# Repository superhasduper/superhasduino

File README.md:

# superhasduino
its a comercial prototiping board
if you want to access the pcb files use kicad

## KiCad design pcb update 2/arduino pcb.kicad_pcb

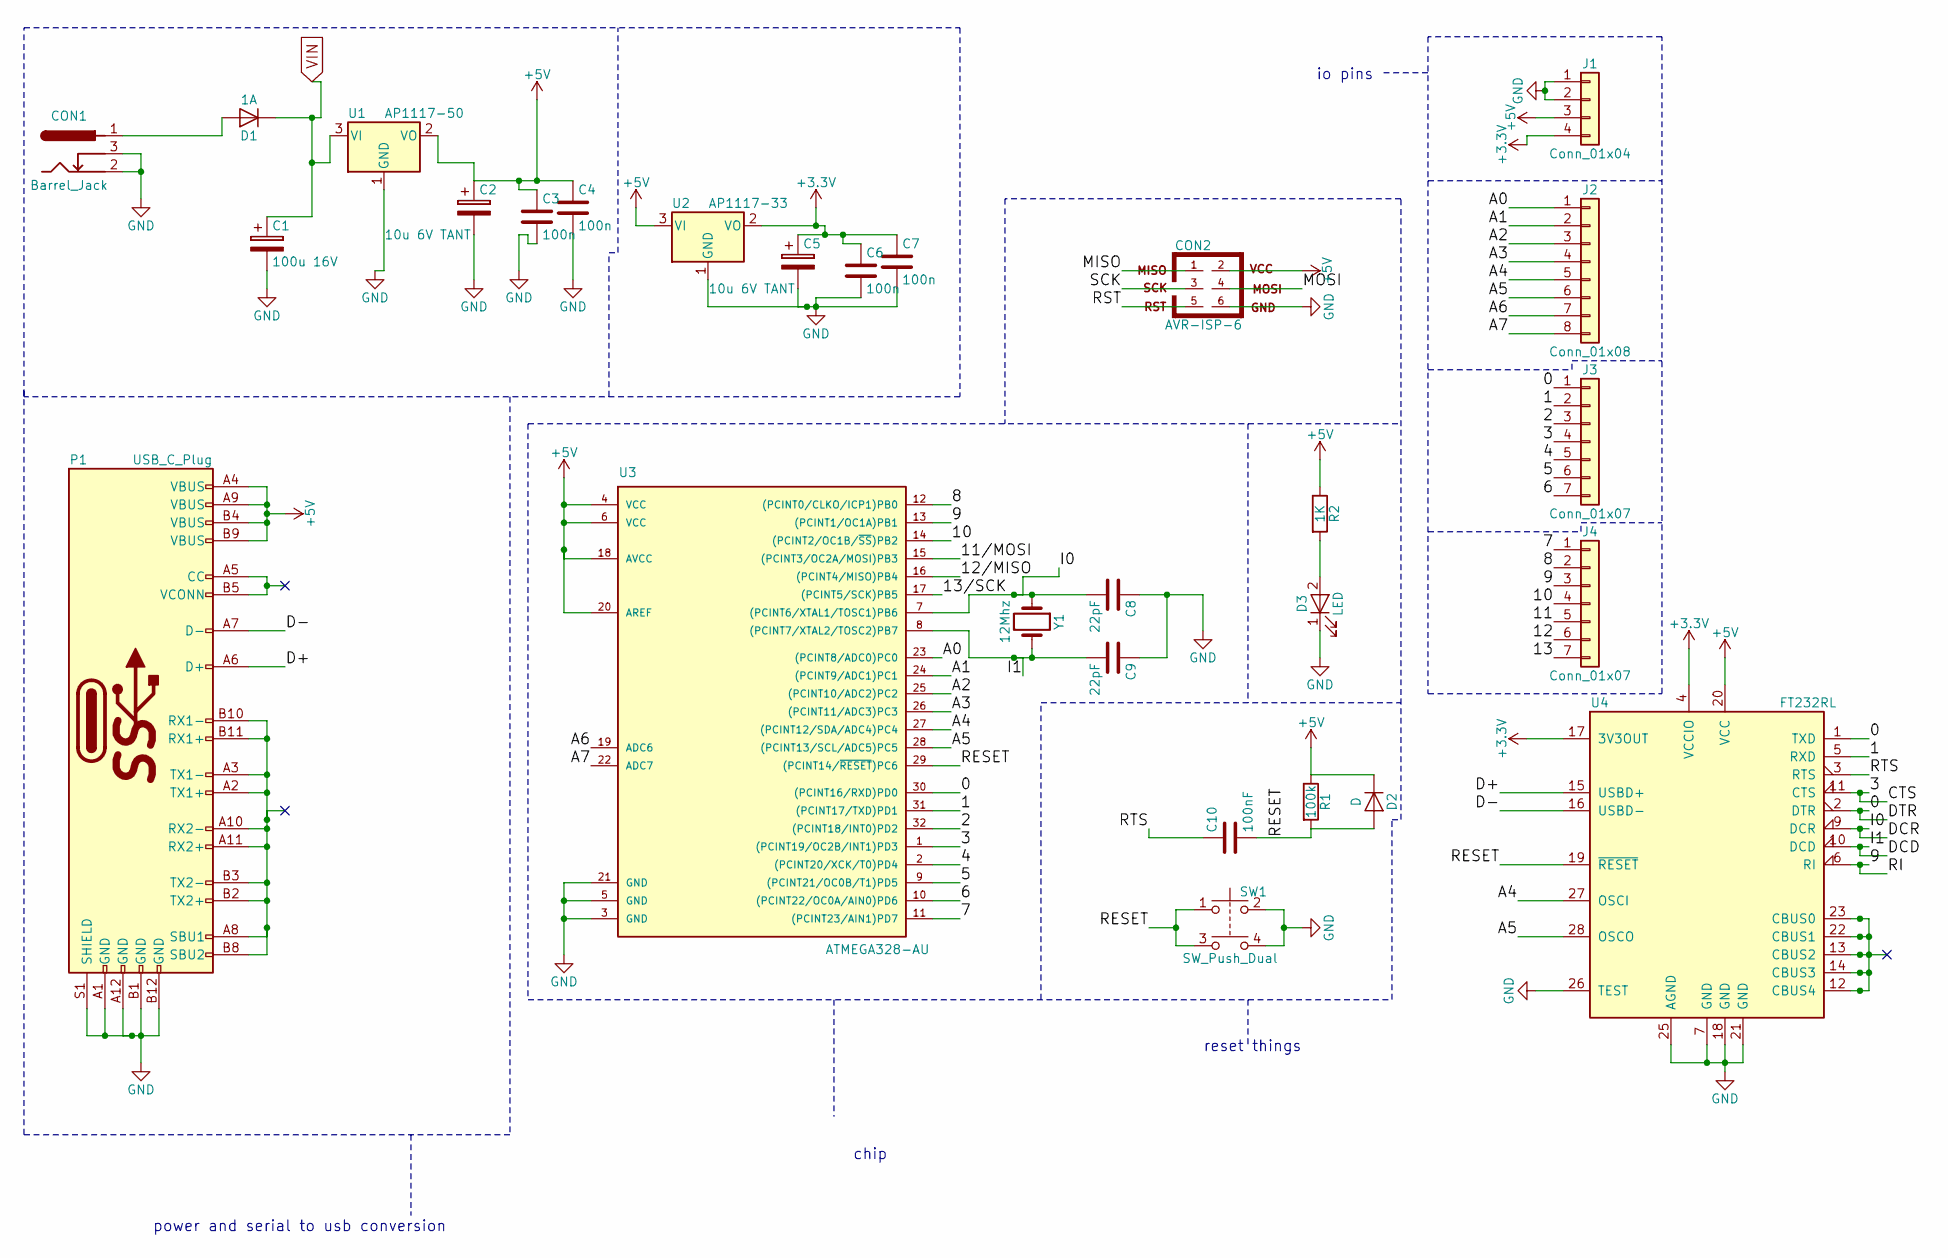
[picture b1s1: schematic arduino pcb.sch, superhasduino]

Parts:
C1: 100u 16V; CP_Radial_D4.0mm_P2.00mm
C2, C5: 10u 6V TANT; CP_Radial_D4.0mm_P2.00mm
C3, C4, C6, C7: 100n; C_1206_HandSoldering
C8, C9: 22pF; C_1206_HandSoldering
C10: 100nF; C_1206_HandSoldering
CON1: Barrel_Jack; BARREL_JACK
CON2: AVR-ISP-6; Pin_Header_Straight_2x03_Pitch2.00mm
D1: 1A; D_1206
D2: D; D_1206
D3: LED; LED_1206_HandSoldering
J1: Conn_01x04; Pin_Header_Straight_1x04_Pitch2.54mm
J2: Conn_01x08; Socket_Strip_Straight_1x08_Pitch2.54mm
J3, J4: Conn_01x07; Pin_Header_Straight_1x07_Pitch2.54mm
P1: USB_C_Plug; USB_C_Plug_Molex_105444
R1: 100k; R_1206_HandSoldering
R2: 1K; R_1206_HandSoldering
SW1: SW_Push_Dual; SW_TH_Tactile_Omron_B3F-10xx
U1: AP1117-50; SOT-223-3Lead_TabPin2
U2: AP1117-33; SOT-223-3Lead_TabPin2
U3: ATMEGA328-AU; TQFP-32_7x7mm_Pitch0.8mm
U4: FT232RL; SSOP-28_5.3x10.2mm_Pitch0.65mm
Y1: 12Mhz; Crystal_HC18-U_Vertical

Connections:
+3V3: C5.1, C6.1, C7.1, J1.4, U2.2 (VO), U4.4 (VCCIO), U4.17 (3V3OUT)
+5V: C2.1, C3.1, C4.1, CON2.2, D2.1 (K), J1.3, P1.A4 (VBUS), P1.A9 (VBUS), P1.B4 (VBUS), P1.B9 (VBUS), R1.1, R2.1, U1.2 (VO), U2.3 (VI), U3.4 (VCC), U3.6 (VCC), U3.18 (AVCC), U3.20 (AREF), U4.20 (VCC)
/0: J3.1, U3.30 ((PCINT16/RXD)PD0), U4.1 (TXD), U4.2 (DTR)
/1: J3.2, U3.31 ((PCINT17/TXD)PD1), U4.5 (RXD)
/2: J3.3, U3.32 ((PCINT18/INT0)PD2)
/3: J3.4, U3.1 ((PCINT19/OC2B/INT1)PD3), U4.11 (CTS)
/4: J3.5, U3.2 ((PCINT20/XCK/T0)PD4)
/5: J3.6, U3.9 ((PCINT21/OC0B/T1)PD5)
/6: J3.7, U3.10 ((PCINT22/OC0A/AIN0)PD6)
/7: J4.1, U3.11 ((PCINT23/AIN1)PD7)
/8: J4.2, U3.12 ((PCINT0/CLKO/ICP1)PB0)
/9: J4.3, U3.13 ((PCINT1/OC1A)PB1), U4.6 (RI)
/10: J4.4, U3.14 ((PCINT2/OC1B/~SS~)PB2)
/11: J4.5
/11/MOSI: U3.15 ((PCINT3/OC2A/MOSI)PB3)
/12: J4.6
/12/MISO: U3.16 ((PCINT4/MISO)PB4)
/13: J4.7
/13/SCK: U3.17 ((PCINT5/SCK)PB5)
/A0: J2.1, U3.23 ((PCINT8/ADC0)PC0)
/A1: J2.2, U3.24 ((PCINT9/ADC1)PC1)
/A2: J2.3, U3.25 ((PCINT10/ADC2)PC2)
/A3: J2.4, U3.26 ((PCINT11/ADC3)PC3)
/A4: J2.5, U3.27 ((PCINT12/SDA/ADC4)PC4), U4.27 (OSCI)
/A5: J2.6, U3.28 ((PCINT13/SCL/ADC5)PC5), U4.28 (OSCO)
/A6: J2.7, U3.19 (ADC6)
/A7: J2.8, U3.22 (ADC7)
/D+: P1.A6 (D+), U4.15 (USBD+)
/D-: P1.A7 (D-), U4.16 (USBD-)
/DCD: C9.2, U3.8 ((PCINT7/XTAL2/TOSC2)PB7), U4.10 (DCD), Y1.2
/DCR: C8.2, U3.7 ((PCINT6/XTAL1/TOSC1)PB6), U4.9 (DCR), Y1.1
/MISO: CON2.1
/MOSI: CON2.4
/RESET: C10.2, D2.2 (A), R1.2, SW1.1, SW1.3, U3.29 ((PCINT14/~RESET~)PC6), U4.19 (~RESET~)
/RST: CON2.5
/RTS: C10.1, U4.3 (RTS)
/SCK: CON2.3
GND: C1.2, C2.2, C3.2, C4.2, C5.2, C6.2, C7.2, C8.1, C9.1, CON1.2, CON1.3, CON2.6, D3.1 (K), J1.1, J1.2, P1.A1 (GND), P1.A12 (GND), P1.B1 (GND), P1.B12 (GND), P1.S1 (SHIELD), SW1.2, SW1.4, U1.1 (GND), U2.1 (GND), U3.3 (GND), U3.5 (GND), U3.21 (GND), U4.7 (GND), U4.18 (GND), U4.21 (GND), U4.25 (AGND), U4.26 (TEST)
unnamed: CON1.1, D1.2 (A)
unnamed: D3.2 (A), R2.2
unnamed: P1.A5 (CC), P1.B5 (VCONN)
unnamed: P1.A2 (TX1+), P1.A3 (TX1-), P1.A8 (SBU1), P1.A10 (RX2-), P1.A11 (RX2+), P1.B2 (TX2+), P1.B3 (TX2-), P1.B8 (SBU2), P1.B10 (RX1-), P1.B11 (RX1+)
unnamed: U4.12 (CBUS4), U4.13 (CBUS2), U4.14 (CBUS3), U4.22 (CBUS1), U4.23 (CBUS0)
VIN: C1.1, D1.1 (K), U1.3 (VI)

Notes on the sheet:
io pins
power and serial to usb conversion
chip
reset things

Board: 2 copper layers, 26 parts (0 on the bottom side), 34 nets, no tracks yet.

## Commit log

2018-06-16 the schematic is almost done
    everything is almost done but the uart usb conversion
2018-06-16 update 2
    the schematic is complete only the conections on the phisical pcb are left
